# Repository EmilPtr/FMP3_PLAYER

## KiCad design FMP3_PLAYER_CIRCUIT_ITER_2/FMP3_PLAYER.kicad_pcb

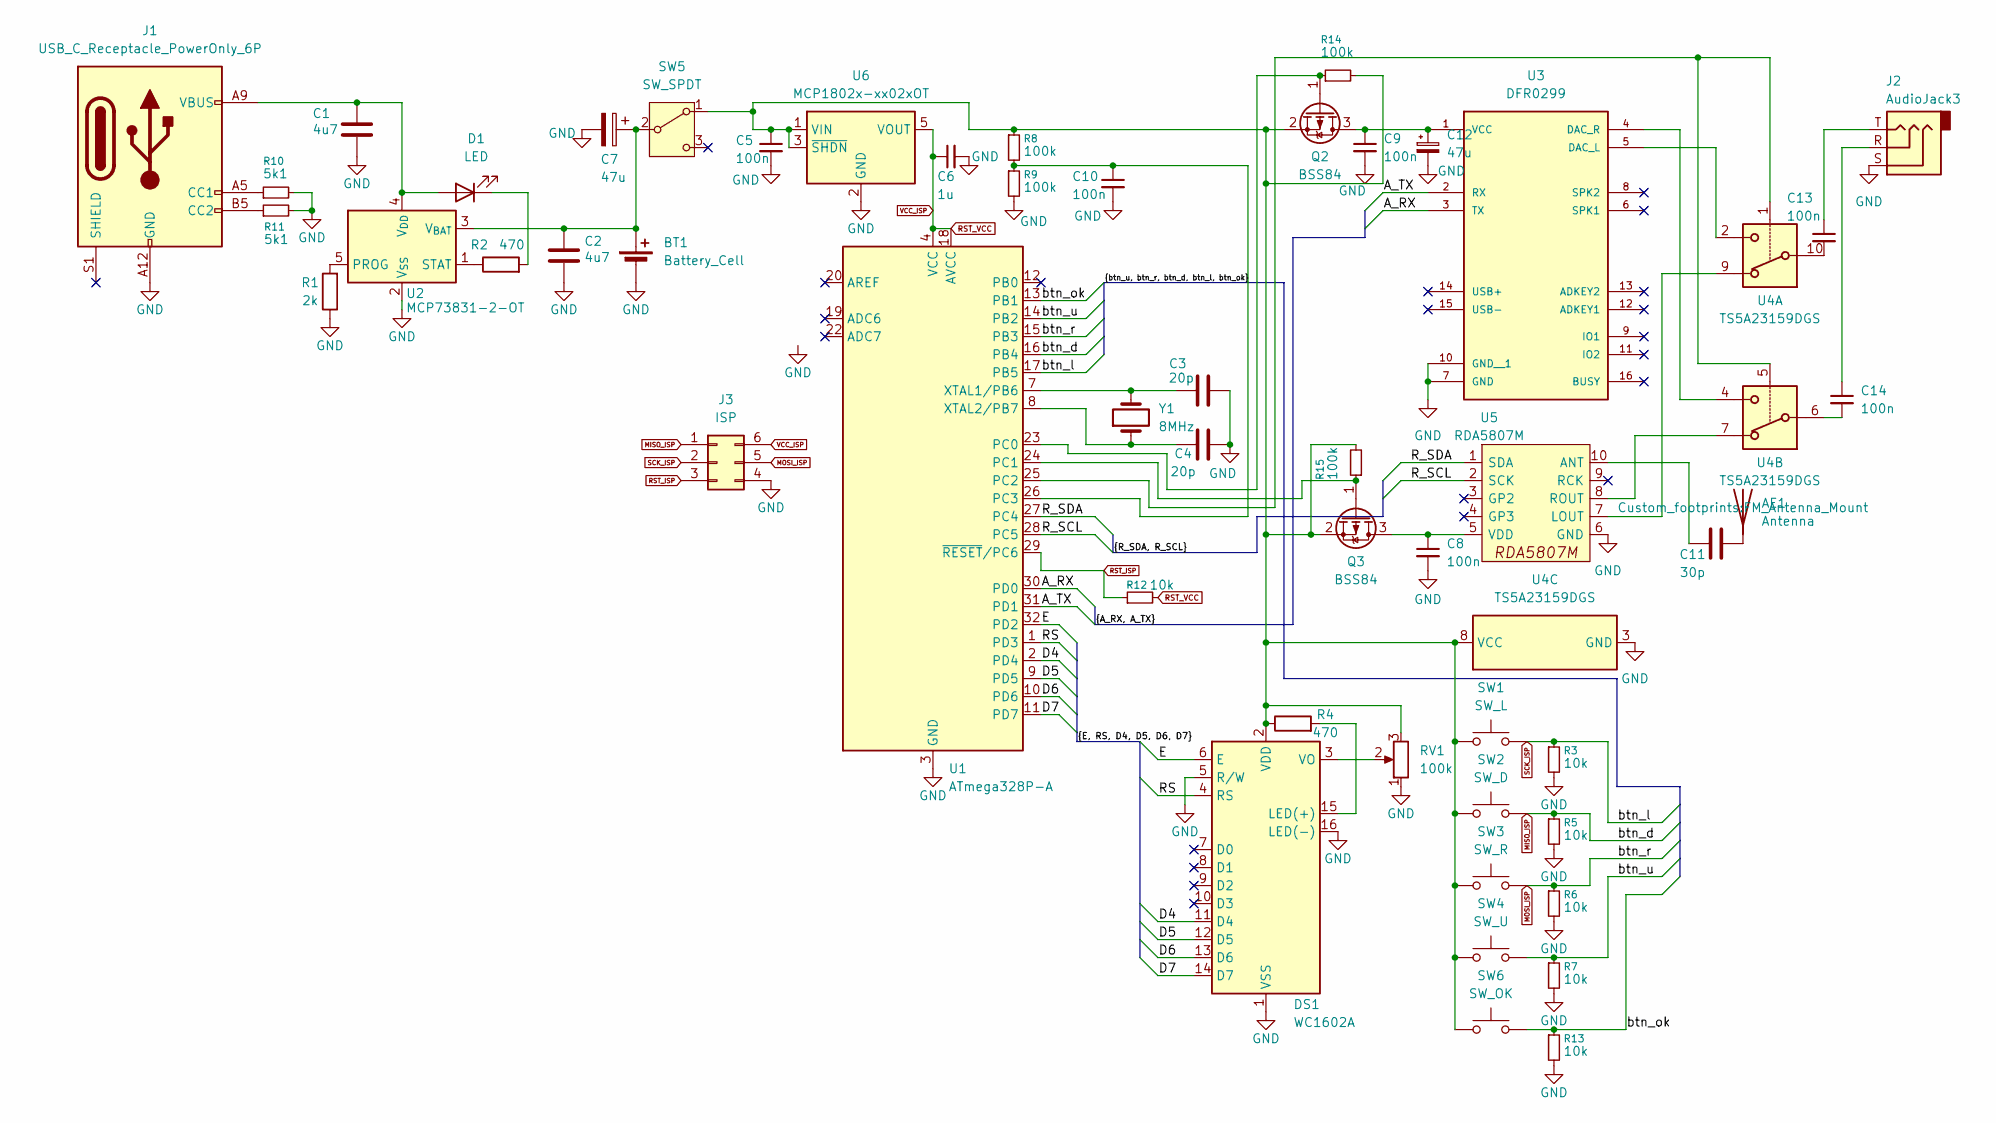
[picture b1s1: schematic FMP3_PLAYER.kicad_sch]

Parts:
AE1: Antenna; FM_Antenna_Mount
BT1: Battery_Cell; JST_PH_B2B-PH-K_1x02_P2.00mm_Vertical
C1, C2: 4u7; C_0805_2012Metric_Pad1.18x1.45mm_HandSolder
C3, C4: 20p; C_0805_2012Metric_Pad1.18x1.45mm_HandSolder
C5, C8, C9, C10, C13, C14: 100n; C_0805_2012Metric_Pad1.18x1.45mm_HandSolder
C6: 1u; C_0805_2012Metric_Pad1.18x1.45mm_HandSolder
C7, C12: 47u; CP_Radial_D5.0mm_P2.50mm
C11: 30p; C_0805_2012Metric_Pad1.18x1.45mm_HandSolder
D1: LED; LED_D5.0mm
DS1: WC1602A; PinSocket_1x16_P2.54mm_Vertical
J1: USB_C_Receptacle_PowerOnly_6P; USB_C_Receptacle_GCT_USB4125-xx-x-0190_6P_TopMnt_Horizontal
J2: AudioJack3; Jack_3.5mm_CUI_SJ-3523-SMT_Horizontal
J3: ISP; PinHeader_2x03_P2.54mm_Vertical
Q2, Q3: BSS84; SOT-23_Handsoldering
R1: 2k; R_0805_2012Metric_Pad1.20x1.40mm_HandSolder
R2, R4: 470; R_0805_2012Metric_Pad1.20x1.40mm_HandSolder
R3, R5, R6, R7, R12, R13: 10k; R_0805_2012Metric_Pad1.20x1.40mm_HandSolder
R8, R9, R14, R15: 100k; R_0805_2012Metric_Pad1.20x1.40mm_HandSolder
R10, R11: 5k1; R_0805_2012Metric_Pad1.20x1.40mm_HandSolder
RV1: 100k; Potentiometer_Bourns_3339P_Vertical
SW1: SW_L; SW_Push_1P1T_NO_CK_KSC9xxG
SW2: SW_D; SW_Push_1P1T_NO_CK_KSC9xxG
SW3: SW_R; SW_Push_1P1T_NO_CK_KSC9xxG
SW4: SW_U; SW_Push_1P1T_NO_CK_KSC9xxG
SW5: SW_SPDT; SW_Slide_SPDT_Angled_CK_OS102011MA1Q
SW6: SW_OK; SW_Push_1P1T_NO_CK_KSC9xxG
U1: ATmega328P-A; TQFP-32_7x7mm_P0.8mm
U2: MCP73831-2-OT; SOT-23-5
U3: DFR0299; MODULE_DFR0299
U4: TS5A23159DGS; VSSOP-10_3x3mm_P0.5mm
U5: RDA5807M; RDA5807M Module
U6: MCP1802x-xx02xOT; SOT-23-5
Y1: 8MHz; Crystal_HC49-4H_Vertical

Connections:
/A_RX: U1.30 (PD0), U3.3 (TX)
/A_TX: U1.31 (PD1), U3.2 (RX)
/D4: DS1.11 (D4), U1.2 (PD4)
/D5: DS1.12 (D5), U1.9 (PD5)
/D6: DS1.13 (D6), U1.10 (PD6)
/D7: DS1.14 (D7), U1.11 (PD7)
/E: DS1.6 (E), U1.32 (PD2)
/RS: DS1.4 (RS), U1.1 (PD3)
/R_SCL: U1.28 (PC5), U5.2 (SCK)
/R_SDA: U1.27 (PC4), U5.1 (SDA)
/btn_ok: R13.1, SW6.2, U1.13 (PB1)
/btn_u: R7.1, SW4.2, U1.14 (PB2)
GND: BT1.2 (-), C1.2, C2.2, C3.2, C4.2, C5.2, C6.2, C7.2, C8.2, C9.2, C10.2, C12.2, DS1.1 (VSS), DS1.5 (R/W), DS1.16 (LED(-)), J1.A12 (GND), J1.B12 (GND), J2.S, J3.4, R1.1, R3.2, R5.2, R6.2, R7.2, R9.2, R10.2, R11.2, R13.2, RV1.1, U1.3 (GND), U1.5 (GND), U1.21 (GND), U2.2 (V_{SS}), U3.7 (GND), U3.10 (GND__1), U4.3 (GND), U5.6 (GND), U6.2 (GND)
MISO_ISP: J3.1, R5.1, SW2.2, U1.16 (PB4)
MOSI_ISP: J3.5, R6.1, SW3.2, U1.15 (PB3)
unnamed: AE1.1 (A), C11.2
unnamed: BT1.1 (+), C2.1, C7.1, SW5.2 (B), U2.3 (V_{BAT})
unnamed: C13.1, J2.T
unnamed: C13.2, U4.10
unnamed: C14.1, J2.R
unnamed: C14.2, U4.6
unnamed: C1.1, D1.2 (A), J1.A9 (VBUS), J1.B9 (VBUS), U2.4 (V_{DD})
unnamed: D1.1 (K), R2.2
unnamed: DS1.15 (LED(+)), R4.2
unnamed: C5.1, DS1.2 (VDD), Q2.2 (S), Q3.2 (S), R4.1, R8.1, R14.2, R15.2, RV1.3, SW1.1, SW2.1, SW3.1, SW4.1, SW5.1 (A), SW6.1, U4.8 (VCC), U6.1 (VIN), U6.3 (~SHDN)
unnamed: DS1.3 (VO), RV1.2
unnamed: J1.A5 (CC1), R10.1
unnamed: J1.B5 (CC2), R11.1
unnamed: C9.1, C12.1, Q2.3 (D), U3.1 (VCC)
unnamed: Q2.1 (G), R14.1, U1.23 (PC0)
unnamed: C8.1, Q3.3 (D), U5.5 (VDD)
unnamed: Q3.1 (G), R15.1, U1.24 (PC1)
unnamed: U1.25 (PC2), U4.1, U4.5
unnamed: C10.1, R8.2, R9.1, U1.26 (PC3)
unnamed: C3.1, U1.7 (XTAL1/PB6), Y1.2
unnamed: C4.1, U1.8 (XTAL2/PB7), Y1.1
unnamed: R1.2, U2.5 (PROG)
unnamed: R2.1, U2.1 (STAT)
unnamed: U3.5 (DAC_L), U4.2
unnamed: U3.4 (DAC_R), U4.4
unnamed: C11.1, U5.10 (ANT)
unnamed: U4.9, U5.7 (LOUT)
unnamed: U4.7, U5.8 (ROUT)
RST_ISP: J3.3, R12.1, U1.29 (~RESET/PC6)
RST_VCC: C6.1, J3.6, R12.2, U1.4 (VCC), U1.6 (VCC), U1.18 (AVCC), U6.5 (VOUT)
SCK_ISP: J3.2, R3.1, SW1.2, U1.17 (PB5)

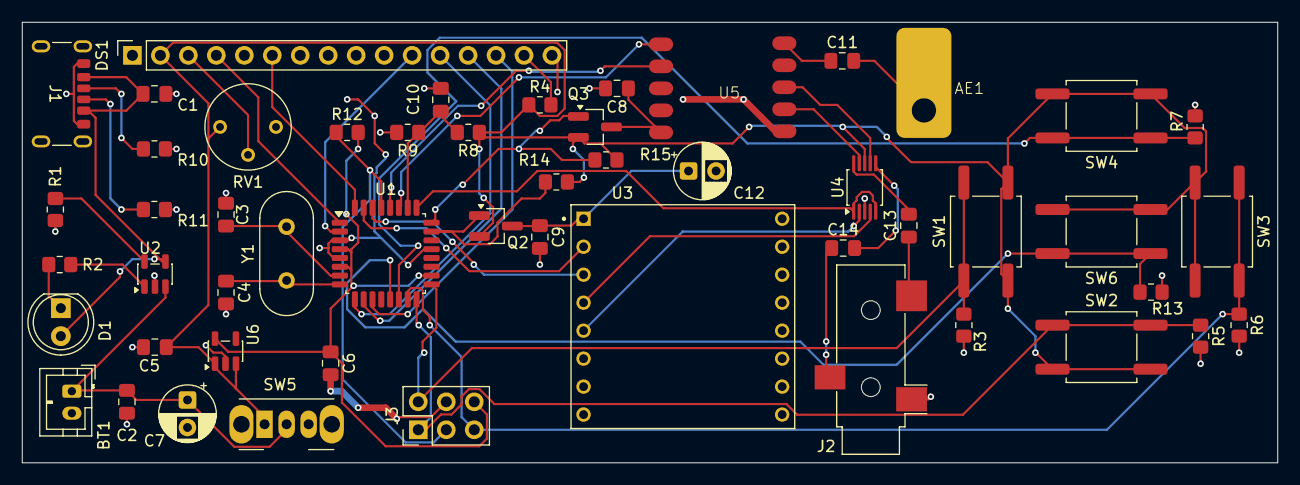
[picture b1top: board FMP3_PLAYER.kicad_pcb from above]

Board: 2 copper layers, 114.0 x 40.0 mm, 52 parts (0 on the bottom side), 46 nets.

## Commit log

2026-02-18 I should probably start tracking work here...
2026-02-19 Started a new iteration cause 4 layer to expensive
2026-02-19 Second iteration complete, much cheaper to manufacture
2026-02-19 sent out for manu, digikey order made, cant wait
2026-02-20 The DFPlayer NEEDS a fat decoupling cap...
2026-02-20 I swear to git this is the final pcb...
2026-02-21 Starting to make the actual firmware
2026-02-22 I realized after some prototyping my PMOS was bad, fixed now, i swear this better be the final...
2026-02-22 minor fix, used pulldowns instead of pullups by accident
2026-02-22 another minor fix, i should really go sleep...
2026-02-23 Firmware fully demonstrates all functionality
2026-02-24 Fully fleshed out the firmware, yet to test
2026-02-24 MP3 works very well, but FM is incredibly broken, maybe the chip is bad? idj
